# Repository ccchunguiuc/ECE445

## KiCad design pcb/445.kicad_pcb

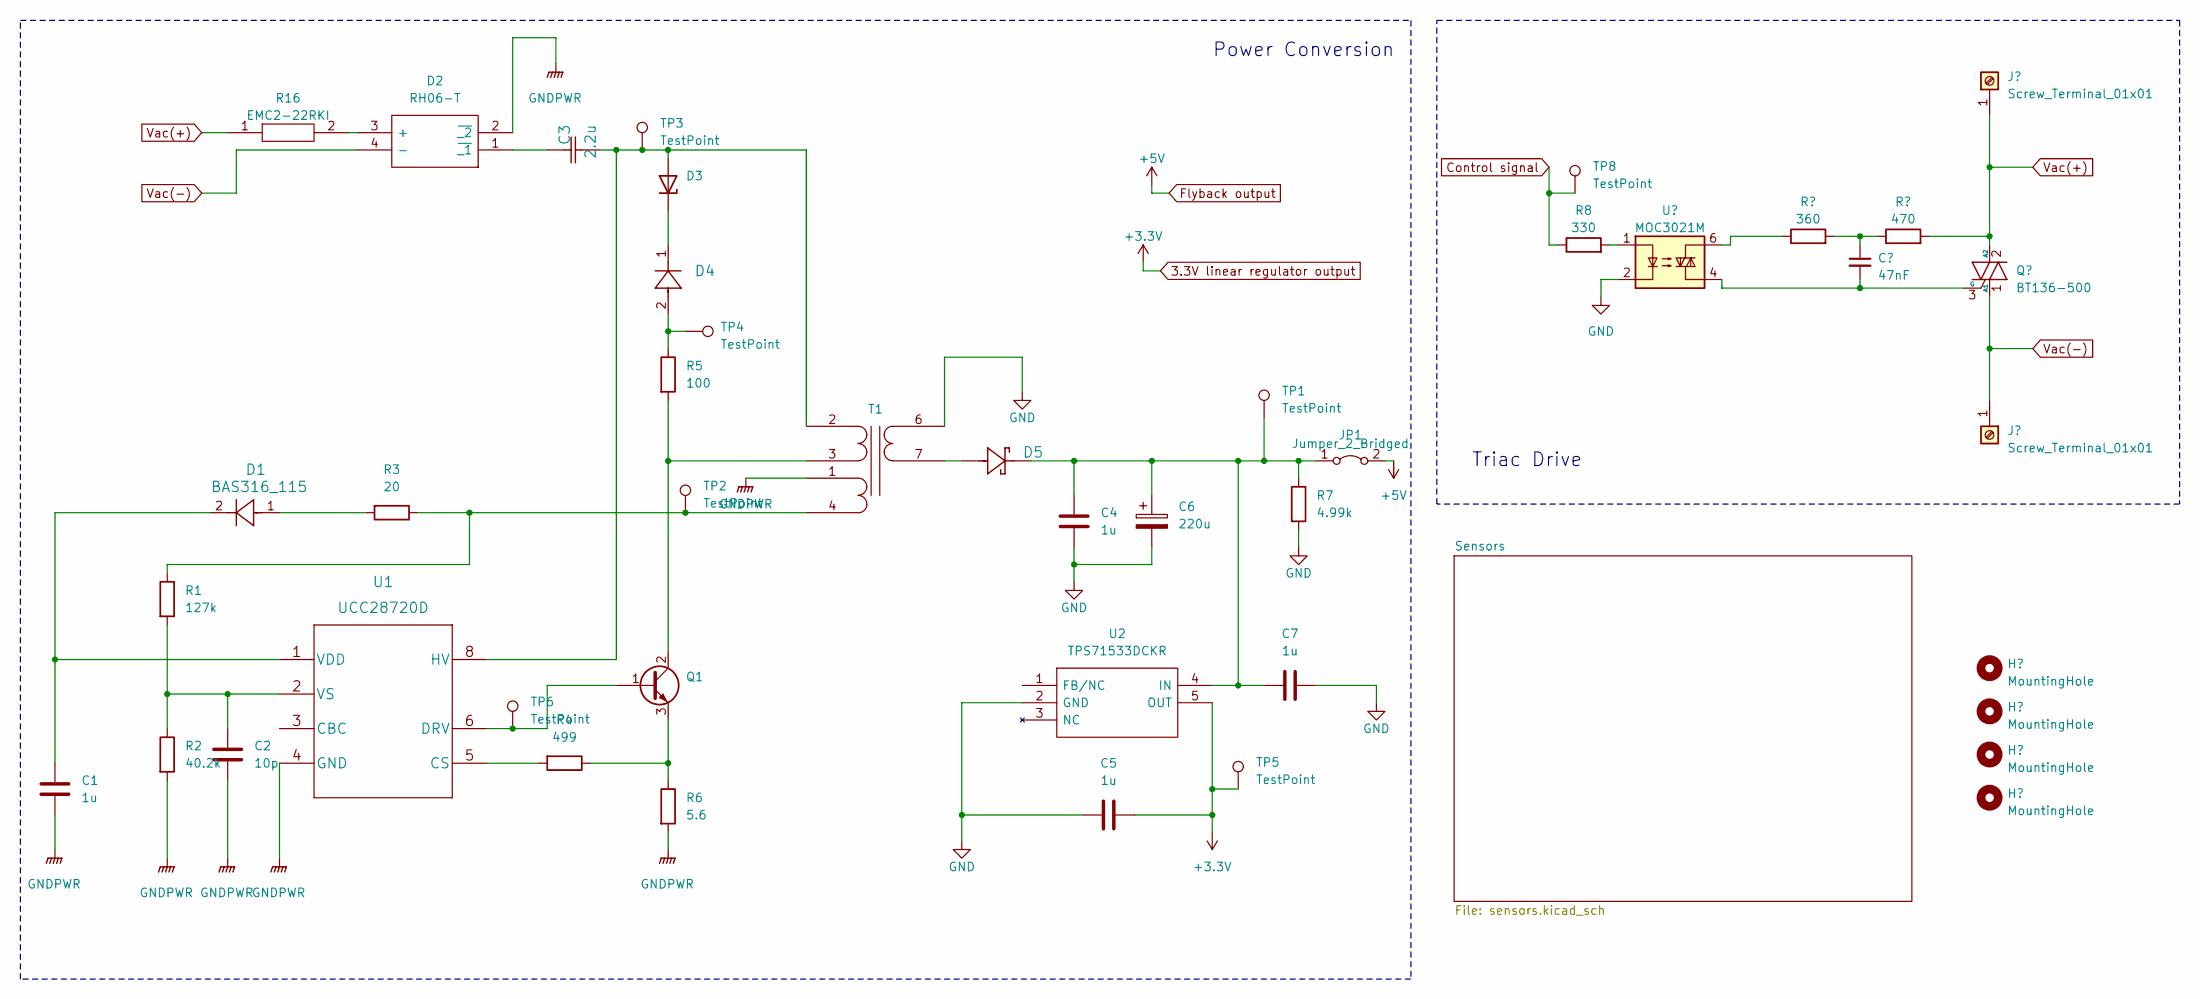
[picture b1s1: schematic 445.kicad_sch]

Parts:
C1, C4, C5, C7: 1u; C_0603_1608Metric
C2: 10p; R_0603_1608Metric
C3: 2.2u; CKG57NX7T2W225M500JH
C6: 220u; 10TPE220ML
C8: 47nF; C_0603_1608Metric
D1: BAS316_115; SC-76_SOD323_NEX
D2: RH06-T; SOP250P700X300-4N; Mouser Part Number 621-RH06-T
D3: D_Zener; SOD-123_ONS
D4: CGRM4007-G; CGRM
D5: SS110-TP; DO-214AC_SMA_HIGHPROFILE_MCC
H1, H2, H3, H4: MountingHole; MountingHole_3.2mm_M3
J1, J2: Screw_Terminal_01x01; MountingHole_8.0mm_M8_Pad_TopBottom
JP1: Jumper_2_Bridged; R_0603_1608Metric
Q1: Q_NPN_BCE; TO-92L
Q2: BT136-500; TO-220-3_Vertical
R1: 127k; R_0402_1005Metric
R2: 40.2k; R_0603_1608Metric
R3: 20; R_0603_1608Metric
R4: 499; R_0603_1608Metric
R5: 100; R_0805_2012Metric
R6: 5.6; R_0805_2012Metric
R7: 4.99k; R_0603_1608Metric
R8: 330; R_0603_1608Metric
R9: 360; R_0603_1608Metric
R10: 470; R_0603_1608Metric
R16: EMC2-22RKI; RESAD2600W80L1000D400; Mouser Part Number 756-EMC2-22RKI
T1: Transformer_SP_1S; 750813314update
TP1, TP2, TP3, TP4, TP5, TP6, TP8: TestPoint; TestPoint_Loop_D3.80mm_Drill2.0mm
U1: UCC28720D
U2: TPS71533DCKR; SOT65P210X110-5N; Mouser Part Number 595-TPS71533DCKR
U3: MOC3021M; MOC3021

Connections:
3.3V linear regulator output: C5.2, TP5.1, U2.5 (OUT); also elsewhere on the board
Control signal: R8.1, TP8.1; also elsewhere on the board
Flyback output: JP1.2 (B); also elsewhere on the board
GND: C4.2, C5.1, C6.2, C7.2, R7.2, T1.6 (S1), U2.2 (GND), U3.2; also elsewhere on the board
GNDPWR: C1.2, C2.2, D2.2 (~_2), R2.2, R6.2, T1.1 (PR2), U1.4 (GND)
unnamed: C8.1, R9.2, R10.1
unnamed: D1.1 (Input), R3.2
unnamed: C1.1, D1.2 (Output), U1.1 (VDD)
unnamed: D2.3 (+), R16.2
unnamed: C3.2, D2.1 (~_1)
unnamed: C3.1, D3.2 (A), T1.2 (PM), TP3.1, U1.8 (HV)
unnamed 26: D3.1 (K), D4.1; also elsewhere on the board
unnamed 27: D4.2, R5.1, TP4.1; also elsewhere on the board
unnamed: C4.1, C6.1, C7.1, D5.2, JP1.1 (A), R7.1, TP1.1, U2.4 (IN)
unnamed: Q1.1 (B), TP6.1, U1.6 (DRV)
unnamed: Q1.2 (C), R5.2, T1.3 (PR2)
unnamed: Q1.3 (E), R4.1, R6.1
unnamed: C8.2, Q2.3 (G), U3.4
unnamed: R1.1, R3.1, T1.4 (PR2), TP2.1
unnamed: R8.2, U3.1
unnamed: R9.1, U3.6
unnamed: D5.1, T1.7 (S2)
unnamed: R4.2, U1.5 (CS)
unnamed: C2.1, R1.2, R2.1, U1.2 (VS)
Vac(+): J1.1, Q2.2 (A2), R10.2, R16.1
Vac(-): D2.4 (-), J2.1, Q2.1 (A1)

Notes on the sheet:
Triac Drive
Power Conversion

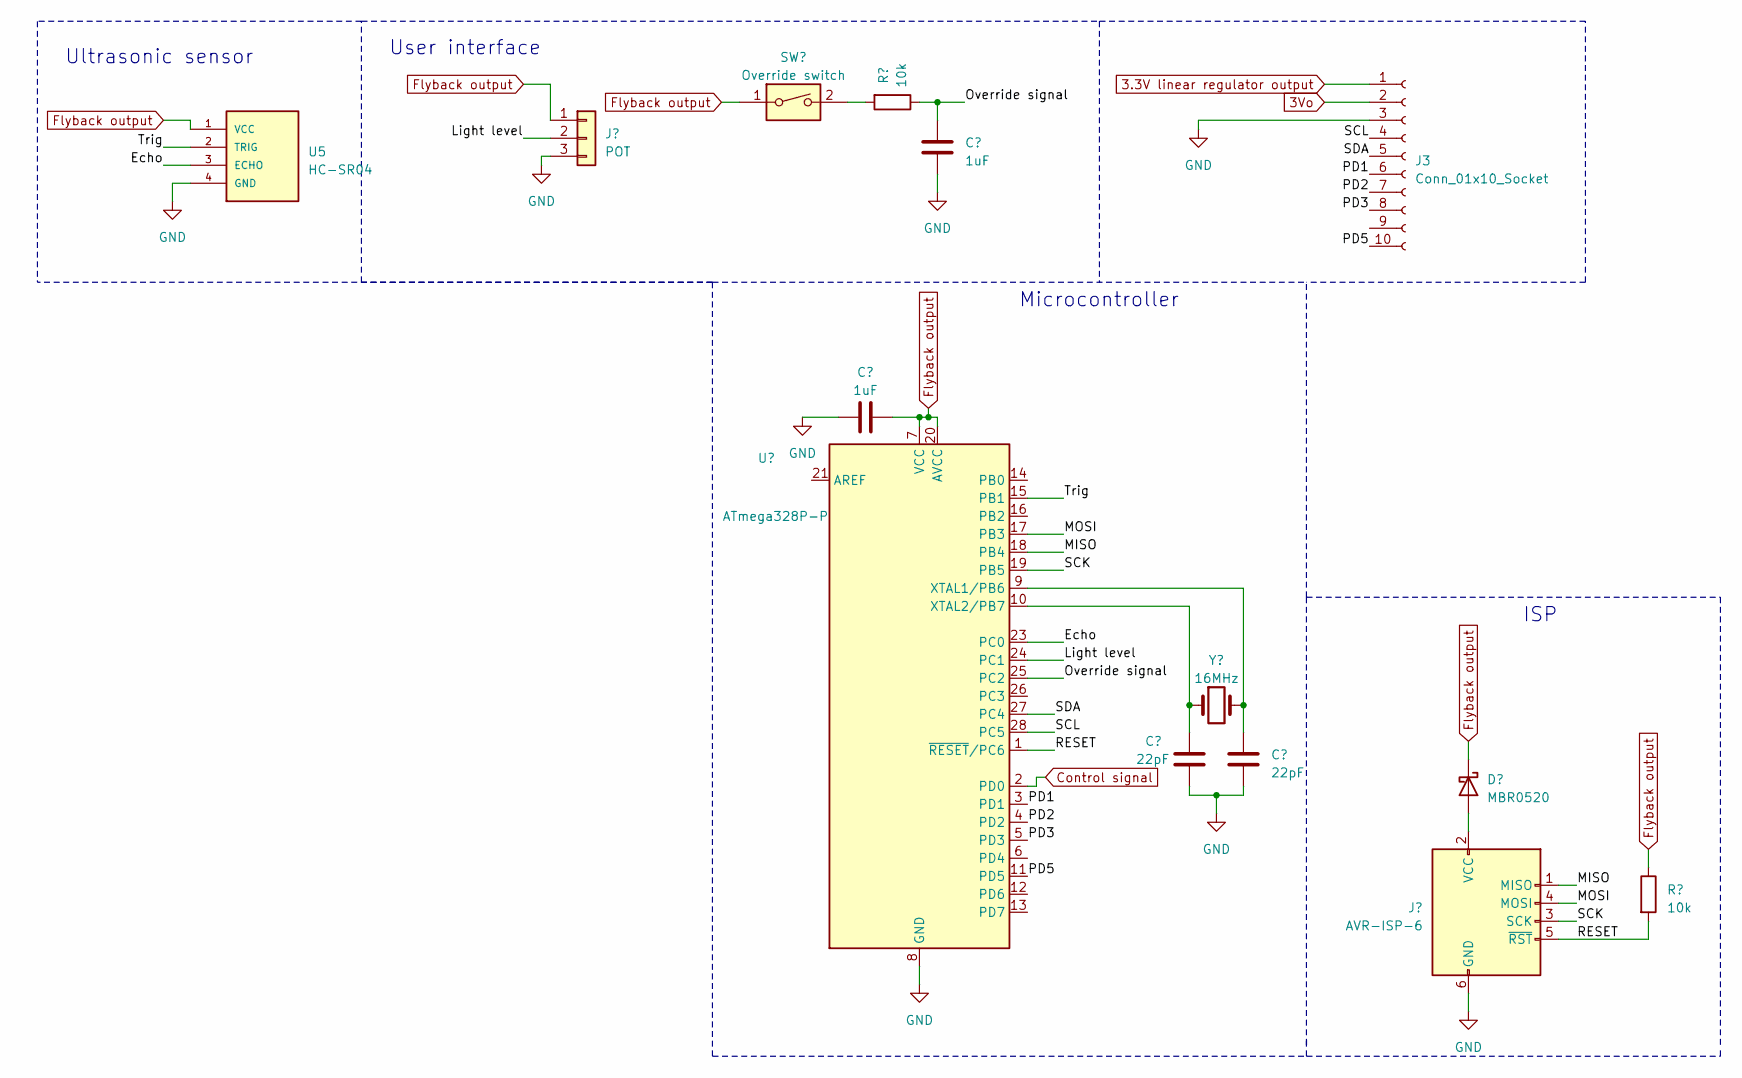
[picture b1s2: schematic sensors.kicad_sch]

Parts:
C11, C14: 1uF; C_0402_1005Metric
C12, C13: 22pF; C_0805_2012Metric
D6: MBR0520; D_SOD-123
J3: Conn_01x10_Socket; PinSocket_1x10_P2.54mm_Vertical
J4: POT; Molex_KK-254_AE-6410-03A_1x03_P2.54mm_Vertical
J5: AVR-ISP-6; IDC-Header_2x03_P2.54mm_Vertical
R14, R15: 10k; R_0603_1608Metric
SW1: Override switch; SW_SPST_CK_KXT3
U4: ATmega328P-P; DIP-28_W7.62mm
U5: HC-SR04; XCVR_HC-SR04
Y1: 16MHz; Crystal_HC49-U_Vertical

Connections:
3.3V linear regulator output: J3.1; also elsewhere on the board
3Vo: J3.2
/Sensors/Echo: U4.23 (PC0), U5.3 (ECHO)
/Sensors/Light level: J4.2, U4.24 (PC1)
/Sensors/MISO: J5.1 (MISO), U4.18 (PB4)
/Sensors/MOSI: J5.4 (MOSI), U4.17 (PB3)
/Sensors/Override signal: C14.1, R15.1, U4.25 (PC2)
/Sensors/PD1: J3.6, U4.3 (PD1)
/Sensors/PD2: J3.7, U4.4 (PD2)
/Sensors/PD3: J3.8, U4.5 (PD3)
/Sensors/PD5: J3.10, U4.11 (PD5)
/Sensors/RESET: J5.5 (~RST), R14.2, U4.1 (~RESET/PC6)
/Sensors/SCK: J5.3 (SCK), U4.19 (PB5)
/Sensors/SCL: J3.4, U4.28 (PC5)
/Sensors/SDA: J3.5, U4.27 (PC4)
/Sensors/Trig: U4.15 (PB1), U5.2 (TRIG)
Control signal: U4.2 (PD0); also elsewhere on the board
Flyback output: C11.2, D6.1 (K), J4.1, R14.1, SW1.1, U4.7 (VCC), U4.20 (AVCC), U5.1 (VCC); also elsewhere on the board
GND: C11.1, C12.2, C13.2, C14.2, J3.3, J4.3, J5.6 (GND), U4.8 (GND), U4.22 (GND), U5.4 (GND); also elsewhere on the board
unnamed: D6.2 (A), J5.2 (VCC)
unnamed: R15.2, SW1.2
unnamed: C13.1, U4.9 (XTAL1/PB6), Y1.2
unnamed: C12.1, U4.10 (XTAL2/PB7), Y1.1

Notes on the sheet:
ISP
Ultrasonic sensor
User interface
Microcontroller

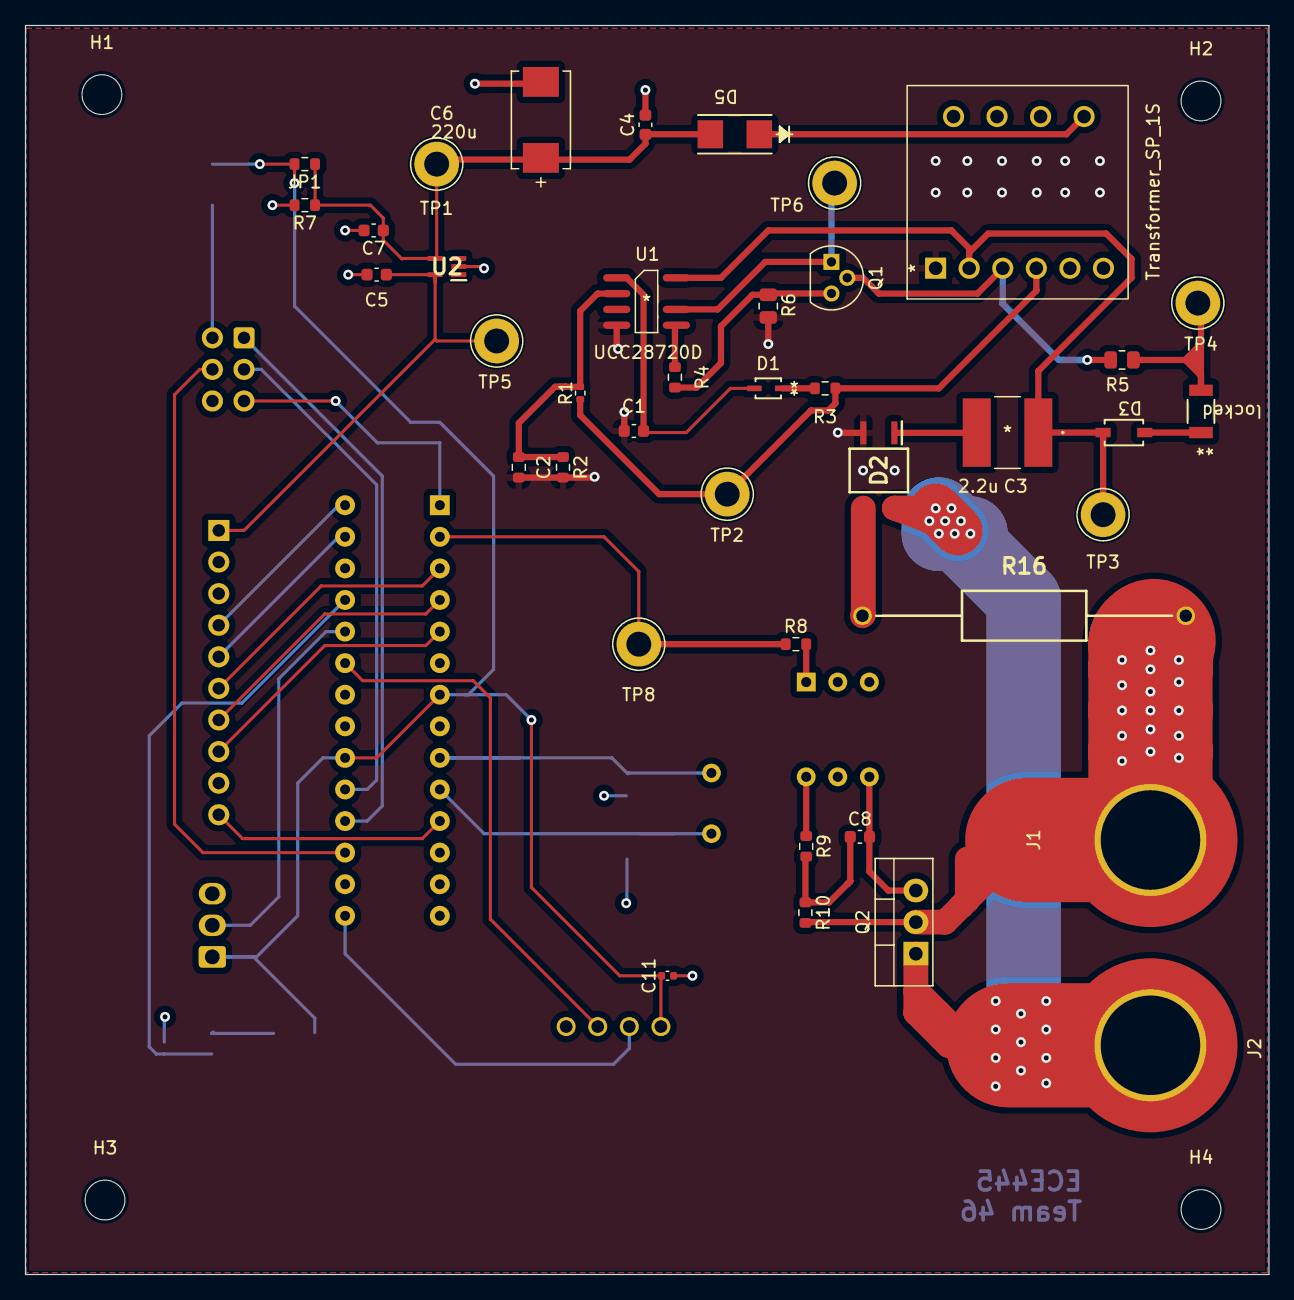
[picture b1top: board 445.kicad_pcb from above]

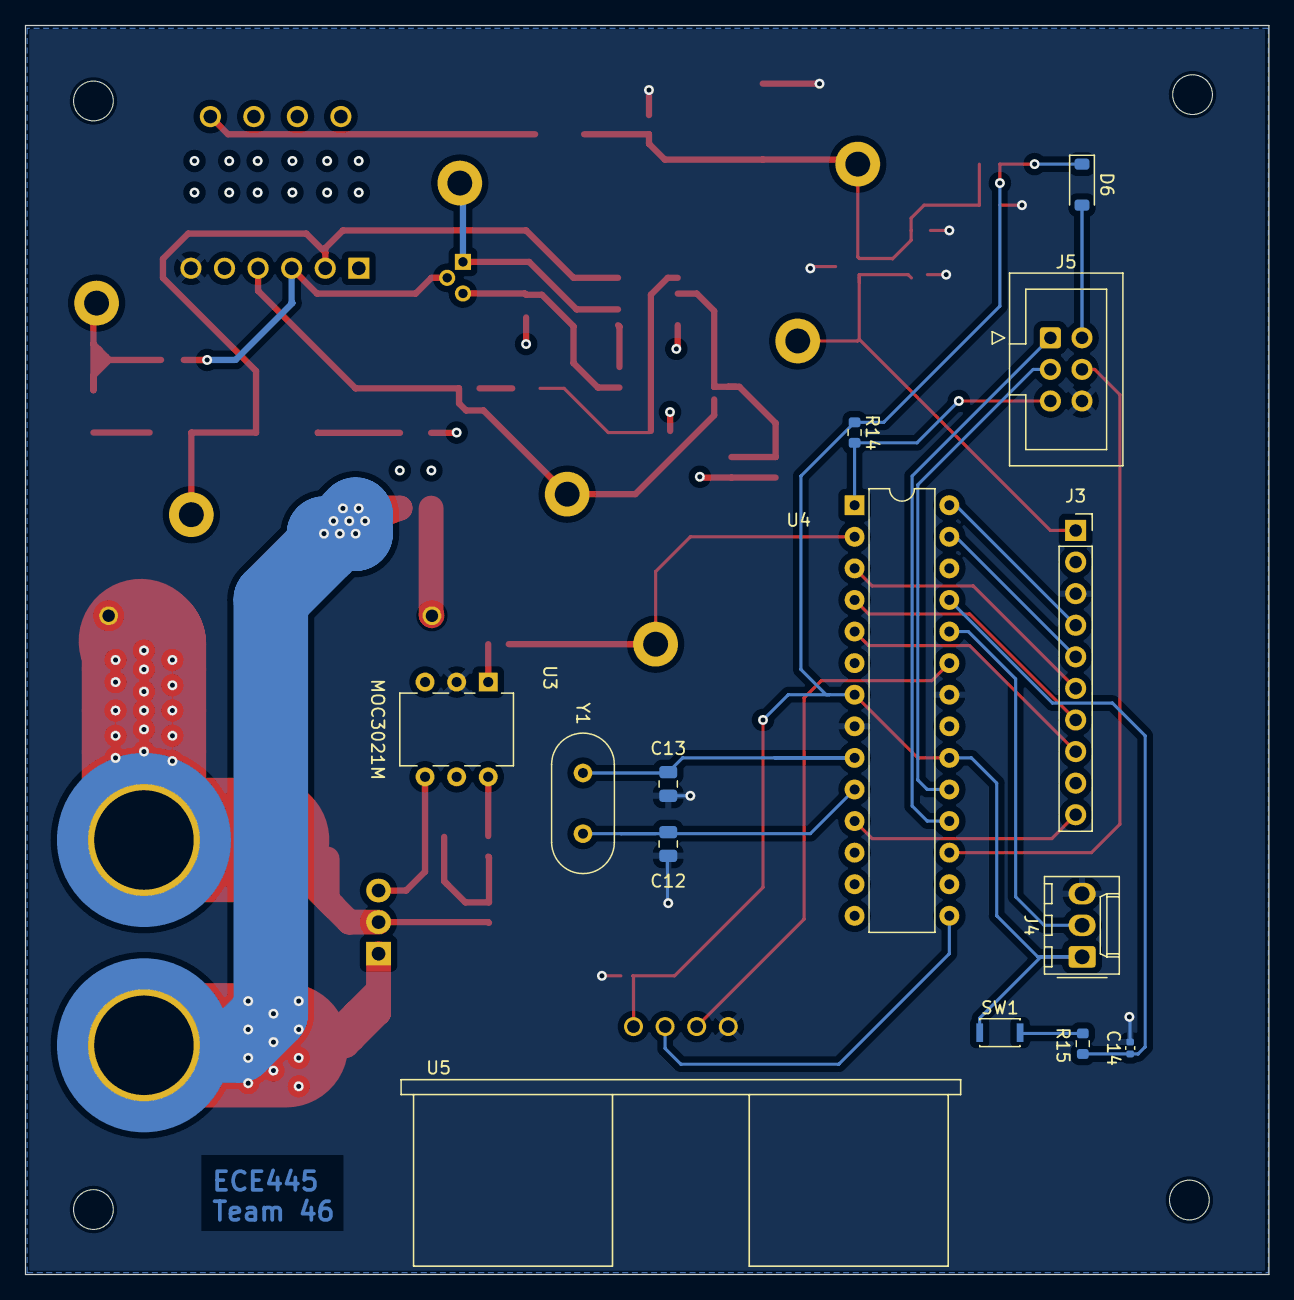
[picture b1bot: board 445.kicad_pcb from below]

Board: 2 copper layers, 100.0 x 100.4 mm, 58 parts (14 on the bottom side), 44 nets.

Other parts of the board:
locked: CGRM4007-G; CGRM

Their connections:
unnamed 26: locked.1; also elsewhere on the board
unnamed 27: locked.2; also elsewhere on the board

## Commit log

2023-03-07 Add sensors sheet
2023-03-07 add power footprints
2023-03-07 symfoot
2023-03-07 File tree restructure
2023-03-07 Add ambient light sensor symbol/footprint
2023-03-07 Restructure symbol and footprint file layout
2023-03-07 Restructure symbols files
2023-03-07 File restructure
2023-03-08 custom footprints added
2023-03-08 Custom symbols added
2023-03-08 Add ultrasonic sensor footprint and symbol
2023-03-08 Final schematic before layout
2023-03-08 Add fuse symbol and footprint
2023-03-08 Almost done with sensors layout
2023-03-08 Routing done
2023-03-08 Fixing DRC issues
2023-03-08 Add gerber files
2023-03-24 Reorganize project folder structure
2023-03-24 Restructure folder format
2023-03-25 Arduino test files for ultrasonic and potentiometer added as well as control code draft
2023-03-29 implemented full PID control logic. to be tested
2023-04-14 added tests for luminosity sensor and pid; updated control code
2023-04-18 Add variable pwm square wave
2023-04-18 Trying to make pwm output for control working
2023-04-18 PWM square wave output working
2023-04-18 Increase P_COST for PID control
2023-04-18 Remove testing code for pot/lux sensor
2023-04-19 Potentiometer incorporated into control
2023-04-20 control code working on arduino
2023-05-04 Final code version
2023-05-04 Restructure project repository
2023-05-04 Remove zip file

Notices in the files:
parts and their libraries:
Copyright 2021 Accelerated Designs. All rights reserved.
